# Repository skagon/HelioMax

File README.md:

# HelioMax
HelioMax is a modular extended variation of the classic split mechanical keyboard, ErgoDox. Optimised for detaching the thumb cluster as well as adding an also detachable F-key row. Please note that this is a **wired** keyboard, designed to have the controller and USB connection in a detached central hub.

## Project Architecture

Unlike traditional monolithic keyboard layouts, **HelioMax** breaks the hardware matrix down into standalone, independent modules. This allows the modification of, or iteration upon, individual sections of the keyboard independently, without needing to re-fabricate the entire board. Within the project you will find two main subdirectories, /FFCs and /Pin_Interconnects, containing the HelioMax PCB files and schematics for plain pin interconnects or FFCs (flexible flat cable) via SMD sockets. These are two variations on the subject, and you will see that the routing is **not** visually identical -- however, it is __functionally__ identical.

The second main feature of the HelioMax is the fact that it is designed to be controlled by a single **modified** Raspberry Pi Pico. Each half of the HelioMax consists of the central board, which includes all the communication lines to the controller board, as well as the connections to the thumb cluster and F-key row of its side. The entire half is using a 7×7 integrated matrix and each half is designed to be **independently scanned** by the Pico.

## The Pico

The importance of the "modified" part becomes relevant at this point. The **unmodified** Pico only has **23** consecutive GPIO pins available (GPIO0 - GPIO22). However, two halves of the HelioMax require 2×(7+7)=28 GPIO pins. While this is still attainable using a unified row or column scanning, I really wanted the two halves to be independently scanned. The solution was somewhat easy: the Pico *does* have GPIO23-25 present, only assigned to things redundant for this project. With a soldering iron, a scalpel, and some patience, these pins can be liberated and put to use, the result being a contiguous GPIO space starting at GPIO0 and ending at GPIO28 -- and that leaves **one** extra GPIO to do with as we please.
* **GPIO23**  
  Requires cutting two traces next to TestPoint 4 (TP4) on the underside of the Pico PCB and desoldering one tiny resistor near the microUSB port (R8). The signal is now accessible from TP4!  
* **GPIO24**  
Requires desoldering of two tiny resistors (R1, R10) next to the RP2040 chip and soldering a tiny wire on the bottom (common) pads, which will carry the GPIO24 signal.
* **GPIO25**  
Requires desoldering the LED (D2) and replacing its current-limiting resistor (R3) with a tiny piece of wire (or a solder blob). The GPIO25 signal is now accessible from TP5!

Now, the GPIO range is uninterrupted and at our disposal.

Moreover, the PCB itself needs some slight modification, namely filing down the backplane window, as I have made the choice to include full pads rather than castellated pads, in order to reduce manufacturing cost. The _offending_ pads are meant to connect the TP4 and TP5 of the Pico to the PCB.

The repository includes a legacy 4-in-1 master layout blueprint at the root for spatial configuration, alongside four distinct, decoupled sub-projects representing the four "quadrants":

### The Four Quadrants
* **Praetor Enclave (`/Praetor_Enclave`)**  
  The controller board. Houses the Raspberry Pi Pico micro-controller and connections to the two halves (Rows and Columns) on four separate JST-SH sockets.
* **Corpus Sedes (`/Corpus_Sedes`)**  
  The main mechanical switch matrix body. Serves as the primary foundation for your standard alpha-numeric typing layout.
* **Telorum Belt (`/Telorum_Belt`)**  
  The function top row. Positioned specifically above the main matrix (Corpus Sedes) to the exact position F-keys should be. The connection is regular pins or FFC and can be lined up with mounting holes aligned. Recommending 5mm vertical gap.
* **Pollex Cluster (`/Pollex_Cluster`)**  
  The specialized ergonomic thumb cluster extension, now able to be angled to leverage natural thumb position for primary keys like Space, Enter, Layer control, or whatever suits your typing style. Connects to Corpus Sedes either through pins or FFC.

## Manufacturing & Gerber Instructions

Each directory operates as its own self-contained KiCad project. Choose your poison (FFC or pins) and go to the appropriate subdirectory. No particular instructions needed.

## Licensing & Contributions

This project is open-source. Feel free to clone the repository and spin up custom branches to match your preferred physical desk ergonomics.

## Support the Project
If you find this design useful or want to support future hardware iterations, consider buying me a coffee! Donations most welcome.

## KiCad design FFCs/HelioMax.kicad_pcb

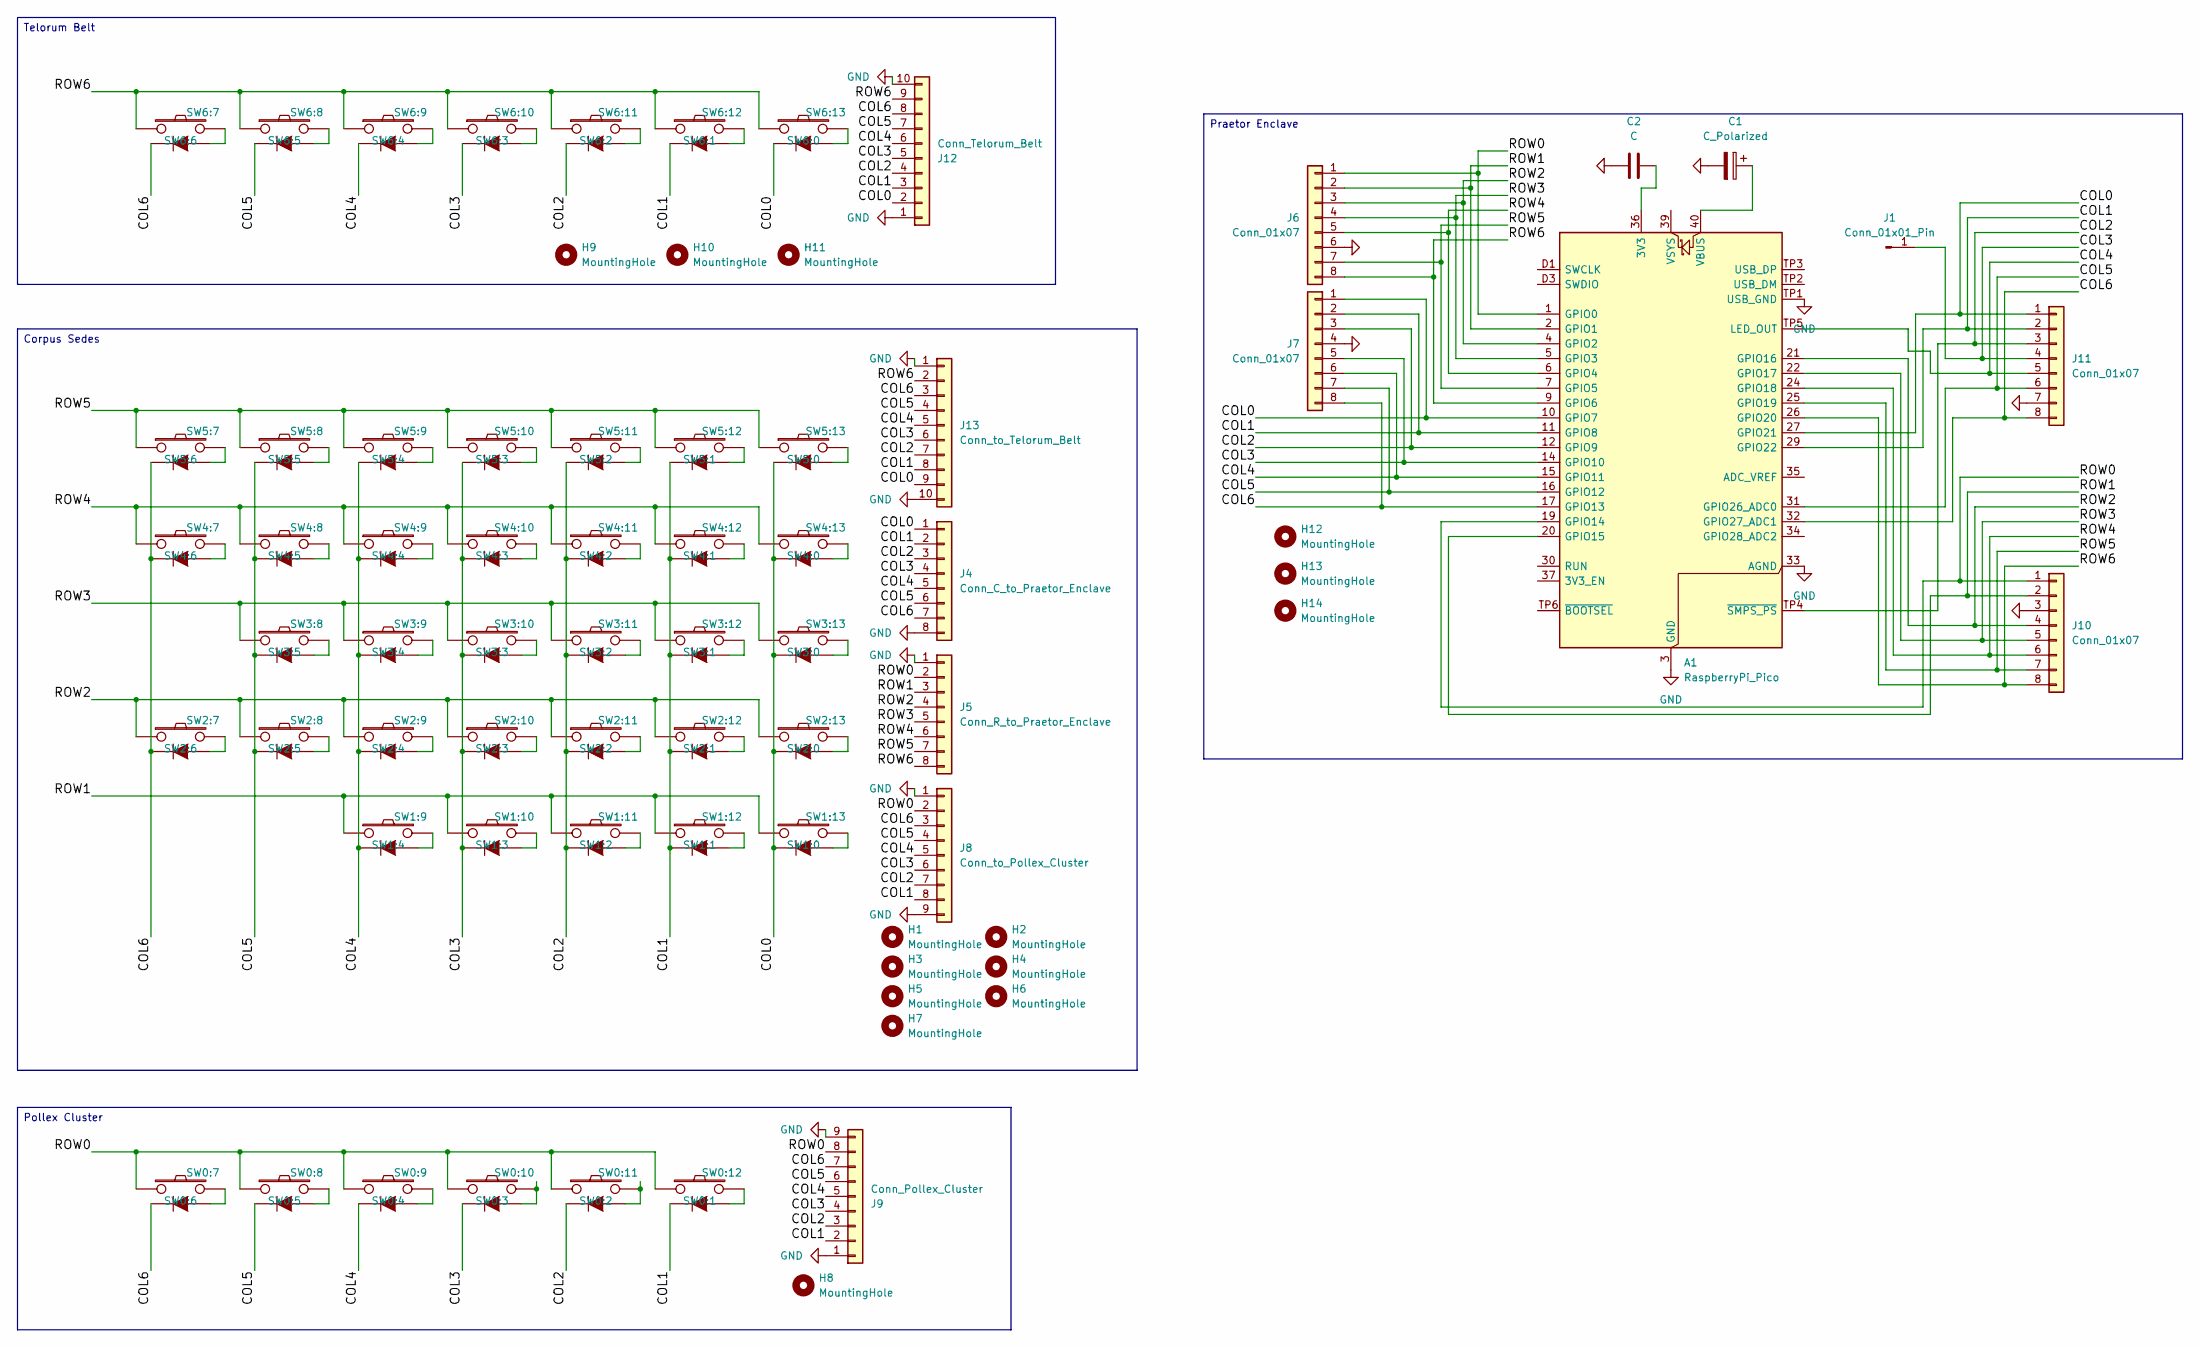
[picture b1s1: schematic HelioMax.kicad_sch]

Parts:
A1: RaspberryPi_Pico; RaspberryPi_Pico_Original_SMD_MountingHoles_HandSolder_Cast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
C1: C_Polarized; CP_Radial_D4.0mm_P2.00mm
C2: C; C_Rect_L7.0mm_W2.5mm_P5.00mm
H1, H2, H3, H4, H5, H6, H7, H8, H9, H10, H11, H12, H13, H14: MountingHole; MountingHole_3.2mm_M3
J1: Conn_01x01_Pin; PinHeader_1x01_P1.00mm_Vertical
J4: Conn_C_to_Praetor_Enclave; JST_SH_SM08B-SRSS-TB_1x08-1MP_P1.00mm_Horizontal
J5: Conn_R_to_Praetor_Enclave; JST_SH_SM08B-SRSS-TB_1x08-1MP_P1.00mm_Horizontal
J6, J7, J10, J11: Conn_01x07; JST_SH_SM08B-SRSS-TB_1x08-1MP_P1.00mm_Horizontal
J8: Conn_to_Pollex_Cluster; Molex_200528-0090_1x09-1MP_P1.00mm_Horizontal
J9: Conn_Pollex_Cluster; Molex_200528-0090_1x09-1MP_P1.00mm_Horizontal
J12: Conn_Telorum_Belt; Molex_200528-0100_1x10-1MP_P1.00mm_Horizontal
J13: Conn_to_Telorum_Belt; Molex_200528-0100_1x10-1MP_P1.00mm_Horizontal
SW0:7: SW0:6; MX_FLIP_CLEAN
SW0:8: SW0:5; MX_FLIP_CLEAN
SW0:9: SW0:4; MX_FLIP_CLEAN
SW0:10: SW0:3; MX_FLIP_CLEAN
SW0:11: SW0:2; MX_FLIP_CLEAN
SW0:12: SW0:1; MX_FLIP_CLEAN
SW1:9: SW1:4; MX_FLIP_CLEAN
SW1:10: SW1:3; MX_FLIP_CLEAN
SW1:11: SW1:2; MX_FLIP_CLEAN
SW1:12: SW1:1; MX_FLIP_CLEAN
SW1:13: SW1:0; MX_FLIP_CLEAN
SW2:7: SW2:6; MX_FLIP_CLEAN
SW2:8: SW2:5; MX_FLIP_CLEAN
SW2:9: SW2:4; MX_FLIP_CLEAN
SW2:10: SW2:3; MX_FLIP_CLEAN
SW2:11: SW2:2; MX_FLIP_CLEAN
SW2:12: SW2:1; MX_FLIP_CLEAN
SW2:13: SW2:0; MX_FLIP_CLEAN
SW3:8: SW3:5; MX_FLIP_CLEAN
SW3:9: SW3:4; MX_FLIP_CLEAN
SW3:10: SW3:3; MX_FLIP_CLEAN
SW3:11: SW3:2; MX_FLIP_CLEAN
SW3:12: SW3:1; MX_FLIP_CLEAN
SW3:13: SW3:0; MX_FLIP_CLEAN
SW4:7: SW4:6; MX_FLIP_CLEAN
SW4:8: SW4:5; MX_FLIP_CLEAN
SW4:9: SW4:4; MX_FLIP_CLEAN
SW4:10: SW4:3; MX_FLIP_CLEAN
SW4:11: SW4:2; MX_FLIP_CLEAN
SW4:12: SW4:1; MX_FLIP_CLEAN
SW4:13: SW4:0; MX_FLIP_CLEAN
SW5:7: SW5:6; MX_FLIP_CLEAN
SW5:8: SW5:5; MX_FLIP_CLEAN
SW5:9: SW5:4; MX_FLIP_CLEAN
SW5:10: SW5:3; MX_FLIP_CLEAN
SW5:11: SW5:2; MX_FLIP_CLEAN
SW5:12: SW5:1; MX_FLIP_CLEAN
SW5:13: SW5:0; MX_FLIP_CLEAN
SW6:7: SW6:6; MX_FLIP_CLEAN
SW6:8: SW6:5; MX_FLIP_CLEAN
SW6:9: SW6:4; MX_FLIP_CLEAN
SW6:10: SW6:3; MX_FLIP_CLEAN
SW6:11: SW6:2; MX_FLIP_CLEAN
SW6:12: SW6:1; MX_FLIP_CLEAN
SW6:13: SW6:0; MX_FLIP_CLEAN

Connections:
/COL0: A1.10 (GPIO7), A1.27 (GPIO21), J4.1, J7.1, J11.1, J12.2, J13.9, SW1:13.4 (K), SW2:13.4 (K), SW3:13.4 (K), SW4:13.4 (K), SW5:13.4 (K), SW6:13.4 (K); also elsewhere on the board
/COL1: A1.11 (GPIO8), A1.29 (GPIO22), J4.2, J7.2, J8.8, J9.2, J11.2, J12.3, J13.8, SW0:12.4 (K), SW1:12.4 (K), SW2:12.4 (K), SW3:12.4 (K), SW4:12.4 (K), SW5:12.4 (K), SW6:12.4 (K); also elsewhere on the board
/COL2: A1.12 (GPIO9), A1.TP4 (~SMPS_PS), J4.3, J7.3, J8.7, J9.3, J11.3, J12.4, J13.7, SW0:11.4 (K), SW1:11.4 (K), SW2:11.4 (K), SW3:11.4 (K), SW4:11.4 (K), SW5:11.4 (K), SW6:11.4 (K); also elsewhere on the board
/COL3: A1.14 (GPIO10), J1.1 (Pin_1_1), J4.4, J7.5, J8.6, J9.4, J11.4, J12.5, J13.6, SW0:10.4 (K), SW1:10.4 (K), SW2:10.4 (K), SW3:10.4 (K), SW4:10.4 (K), SW5:10.4 (K), SW6:10.4 (K); also elsewhere on the board
/COL4: A1.15 (GPIO11), A1.TP5 (LED_OUT), J4.5, J7.6, J8.5, J9.5, J11.5, J12.6, J13.5, SW0:9.4 (K), SW1:9.4 (K), SW2:9.4 (K), SW3:9.4 (K), SW4:9.4 (K), SW5:9.4 (K), SW6:9.4 (K); also elsewhere on the board
/COL5: A1.16 (GPIO12), A1.31 (GPIO26_ADC0), J4.6, J7.7, J8.4, J9.6, J11.6, J12.7, J13.4, SW0:8.4 (K), SW2:8.4 (K), SW3:8.4 (K), SW4:8.4 (K), SW5:8.4 (K), SW6:8.4 (K); also elsewhere on the board
/COL6: A1.17 (GPIO13), A1.32 (GPIO27_ADC1), J4.7, J7.8, J8.3, J9.7, J11.8, J12.8, J13.3, SW0:7.4 (K), SW2:7.4 (K), SW4:7.4 (K), SW5:7.4 (K), SW6:7.4 (K); also elsewhere on the board
/ROW0: A1.1 (GPIO0), A1.19 (GPIO14), J5.2, J6.1, J8.2, J9.8, J10.1, SW0:7.1, SW0:8.1, SW0:9.1, SW0:10.1, SW0:11.1, SW0:12.1; also elsewhere on the board
/ROW1: A1.2 (GPIO1), A1.20 (GPIO15), J5.3, J6.2, J10.2, SW1:9.1, SW1:10.1, SW1:11.1, SW1:12.1, SW1:13.1; also elsewhere on the board
/ROW2: A1.4 (GPIO2), A1.21 (GPIO16), J5.4, J6.3, J10.4, SW2:7.1, SW2:8.1, SW2:9.1, SW2:10.1, SW2:11.1, SW2:12.1, SW2:13.1; also elsewhere on the board
/ROW3: A1.5 (GPIO3), A1.22 (GPIO17), J5.5, J6.4, J10.5, SW3:8.1, SW3:9.1, SW3:10.1, SW3:11.1, SW3:12.1, SW3:13.1; also elsewhere on the board
/ROW4: A1.6 (GPIO4), A1.24 (GPIO18), J5.6, J6.5, J10.6, SW4:7.1, SW4:8.1, SW4:9.1, SW4:10.1, SW4:11.1, SW4:12.1, SW4:13.1; also elsewhere on the board
/ROW5: A1.7 (GPIO5), A1.25 (GPIO19), J5.7, J6.7, J10.7, SW5:7.1, SW5:8.1, SW5:9.1, SW5:10.1, SW5:11.1, SW5:12.1, SW5:13.1; also elsewhere on the board
/ROW6: A1.9 (GPIO6), A1.26 (GPIO20), J5.8, J6.8, J10.8, J12.9, J13.2, SW6:7.1, SW6:8.1, SW6:9.1, SW6:10.1, SW6:11.1, SW6:12.1, SW6:13.1; also elsewhere on the board
GND: A1.3 (GND), A1.8 (GND), A1.13 (GND), A1.18 (GND), A1.23 (GND), A1.28 (GND), A1.33 (AGND), A1.38 (GND), A1.D2 (GND), A1.TP1 (USB_GND), C1.2, C2.2, J4.8, J5.1, J6.6, J6.MP, J7.4, J7.MP, J8.1, J8.9, J8.MP, J9.1, J9.9, J9.MP, J10.3, J10.MP, J11.7, J11.MP, J12.1, J12.10, J12.MP, J13.1, J13.10, J13.MP; also elsewhere on the board
unnamed: A1.36 (3V3), C2.1
unnamed: A1.40 (VBUS), C1.1
unnamed: SW0:7.2, SW0:7.3 (A)
unnamed: SW0:8.2, SW0:8.3 (A)
unnamed: SW0:9.2, SW0:9.3 (A)
unnamed: SW0:10.2, SW0:10.3 (A)
unnamed: SW0:11.2, SW0:11.3 (A)
unnamed: SW0:12.2, SW0:12.3 (A)
unnamed: SW1:9.2, SW1:9.3 (A)
unnamed: SW1:10.2, SW1:10.3 (A)
unnamed: SW1:11.2, SW1:11.3 (A)
unnamed: SW1:12.2, SW1:12.3 (A)
unnamed: SW1:13.2, SW1:13.3 (A)
unnamed: SW2:7.2, SW2:7.3 (A)
unnamed: SW2:8.2, SW2:8.3 (A)
unnamed: SW2:9.2, SW2:9.3 (A)
unnamed: SW2:10.2, SW2:10.3 (A)
unnamed: SW2:11.2, SW2:11.3 (A)
unnamed: SW2:12.2, SW2:12.3 (A)
unnamed: SW2:13.2, SW2:13.3 (A)
unnamed: SW3:8.2, SW3:8.3 (A)
unnamed: SW3:9.2, SW3:9.3 (A)
unnamed: SW3:10.2, SW3:10.3 (A)
unnamed: SW3:11.2, SW3:11.3 (A)
unnamed: SW3:12.2, SW3:12.3 (A)
unnamed: SW3:13.2, SW3:13.3 (A)
unnamed: SW4:7.2, SW4:7.3 (A)
unnamed: SW4:8.2, SW4:8.3 (A)
unnamed: SW4:9.2, SW4:9.3 (A)
unnamed: SW4:10.2, SW4:10.3 (A)
unnamed: SW4:11.2, SW4:11.3 (A)
unnamed: SW4:12.2, SW4:12.3 (A)
unnamed: SW4:13.2, SW4:13.3 (A)
unnamed: SW5:7.2, SW5:7.3 (A)
unnamed: SW5:8.2, SW5:8.3 (A)
unnamed: SW5:9.2, SW5:9.3 (A)
unnamed: SW5:10.2, SW5:10.3 (A)
unnamed: SW5:11.2, SW5:11.3 (A)
unnamed: SW5:12.2, SW5:12.3 (A)
unnamed: SW5:13.2, SW5:13.3 (A)
unnamed: SW6:7.2, SW6:7.3 (A)
unnamed: SW6:8.2, SW6:8.3 (A)
unnamed: SW6:9.2, SW6:9.3 (A)
unnamed: SW6:10.2, SW6:10.3 (A)
unnamed: SW6:11.2, SW6:11.3 (A)
unnamed: SW6:12.2, SW6:12.3 (A)
unnamed: SW6:13.2, SW6:13.3 (A)

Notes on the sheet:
Telorum Belt
Pollex Cluster
Praetor Enclave
Corpus Sedes

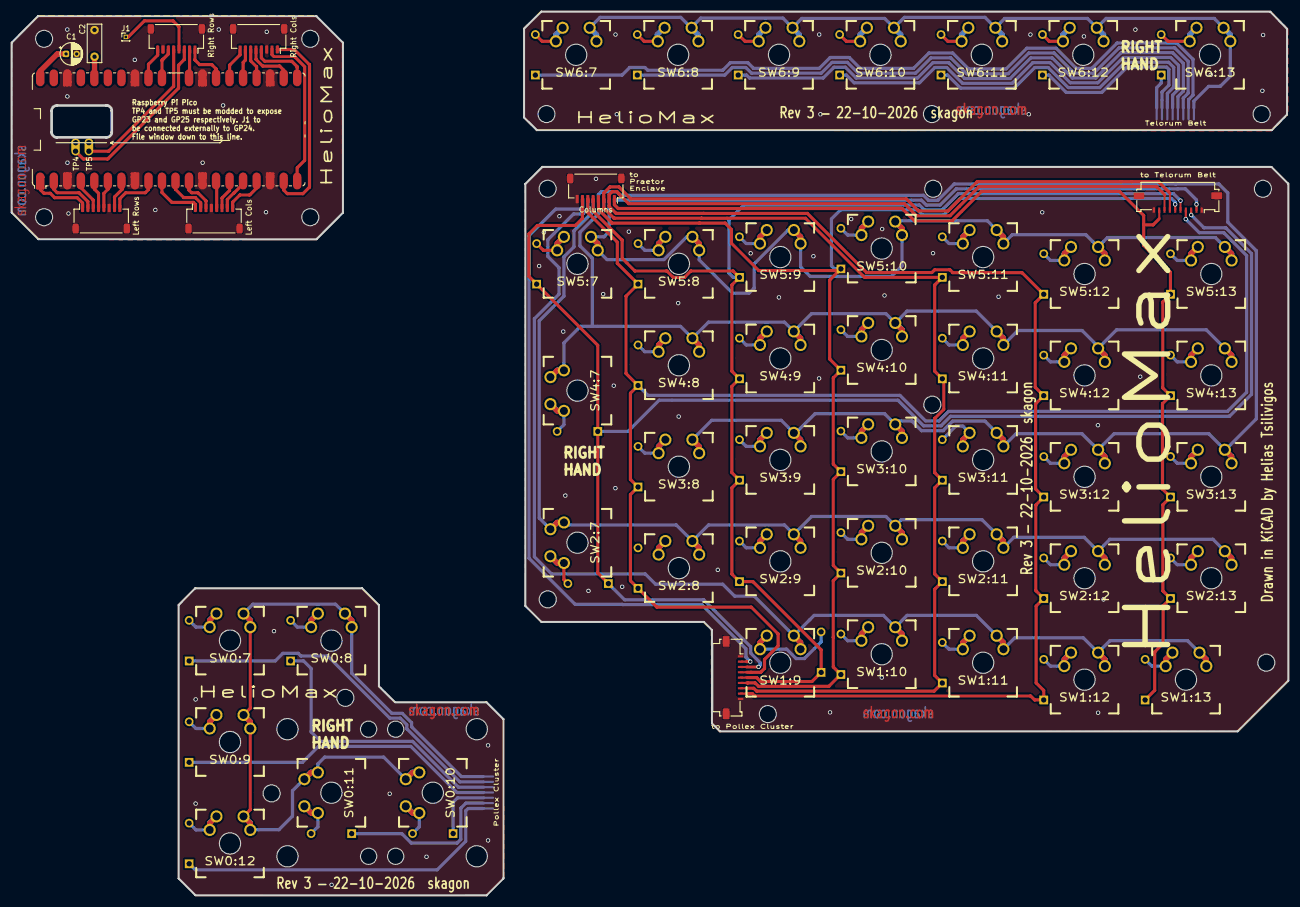
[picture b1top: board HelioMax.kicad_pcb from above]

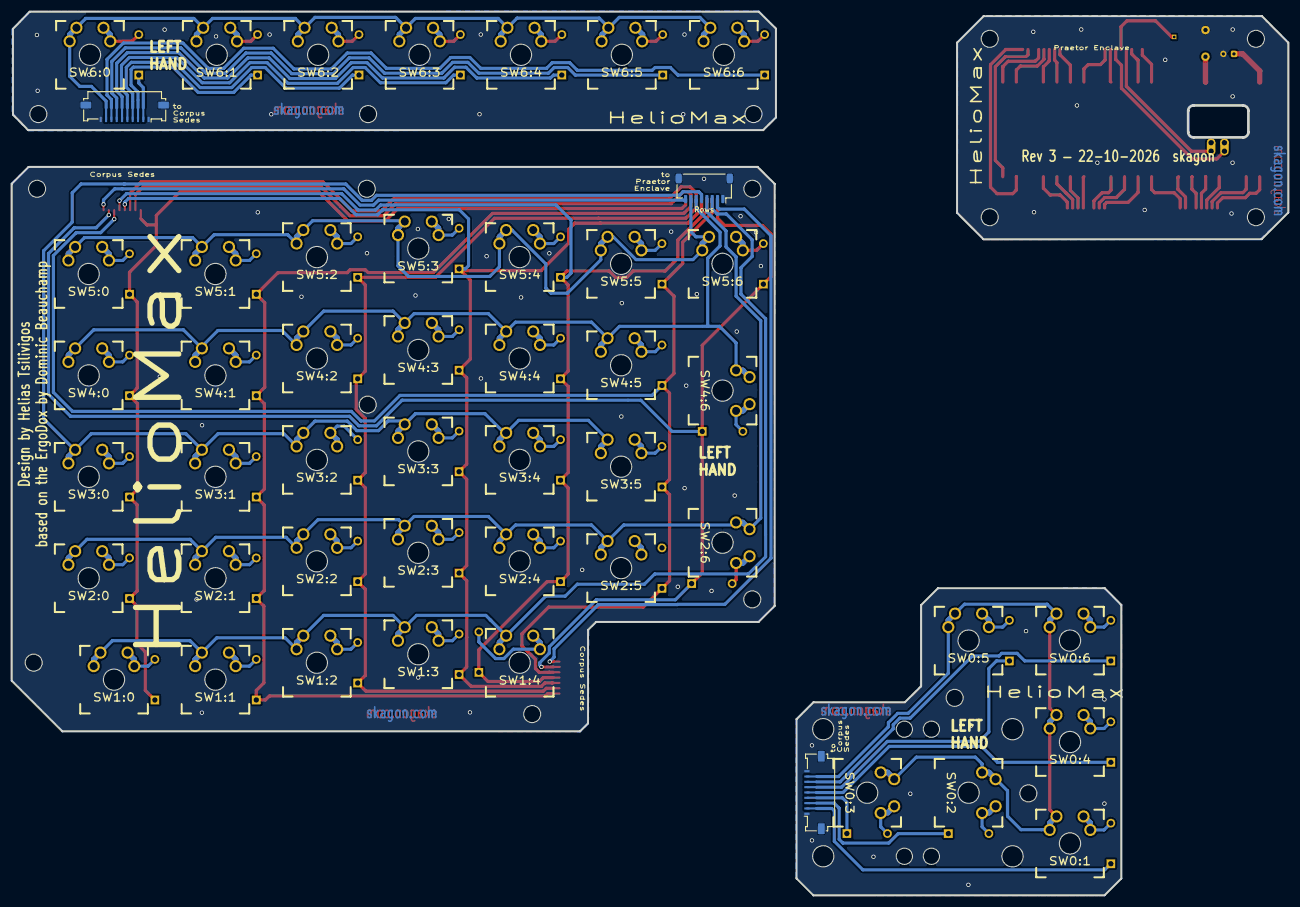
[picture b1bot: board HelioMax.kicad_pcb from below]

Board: 2 copper layers, 239.8 x 166.0 mm, 75 parts (3 on the bottom side), 62 nets.

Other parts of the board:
Columns: Conn_C_to_Praetor_Enclave; JST_SH_SM08B-SRSS-TB_1x08-1MP_P1.00mm_Horizontal
Rows: Conn_R_to_Praetor_Enclave; JST_SH_SM08B-SRSS-TB_1x08-1MP_P1.00mm_Horizontal
S1, S2: STAB200; STAB_PCB940

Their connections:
/COL0: Columns.1; also elsewhere on the board
/COL1: Columns.2; also elsewhere on the board
/COL2: Columns.3; also elsewhere on the board
/COL3: Columns.4; also elsewhere on the board
/COL4: Columns.5; also elsewhere on the board
/COL5: Columns.6; also elsewhere on the board
/COL6: Columns.7; also elsewhere on the board
/ROW0: Rows.2; also elsewhere on the board
/ROW1: Rows.3; also elsewhere on the board
/ROW2: Rows.4; also elsewhere on the board
/ROW3: Rows.5; also elsewhere on the board
/ROW4: Rows.6; also elsewhere on the board
/ROW5: Rows.7; also elsewhere on the board
/ROW6: Rows.8; also elsewhere on the board
GND: Columns.8, Columns.MP, Rows.1, Rows.MP; also elsewhere on the board

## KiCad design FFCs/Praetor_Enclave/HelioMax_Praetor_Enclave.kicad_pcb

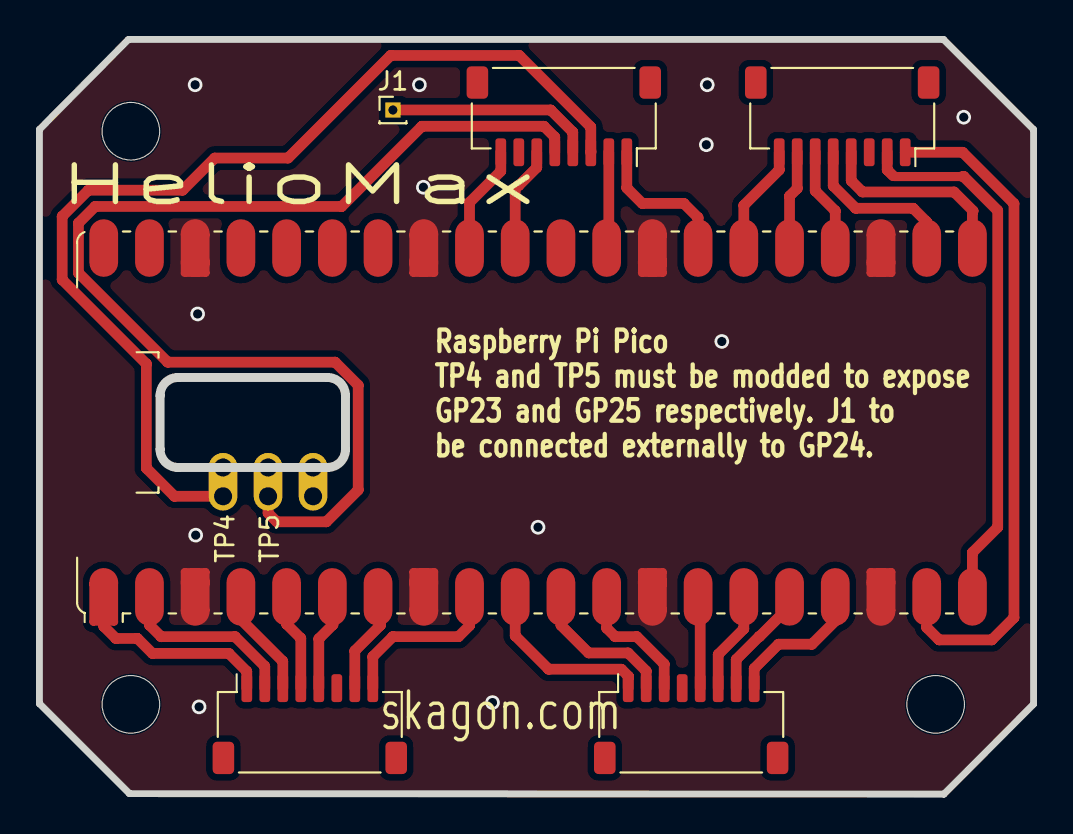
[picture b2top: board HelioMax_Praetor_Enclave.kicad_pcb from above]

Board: 2 copper layers, 55.2 x 41.9 mm, 9 parts (0 on the bottom side), 29 nets.

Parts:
A1: RaspberryPi_Pico; RaspberryPi_Pico_Original_SMD_MountingHoles_HandSolder_Cast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
H12, H13, H14: MountingHole; MountingHole_3.2mm_M3
J1: Conn_01x01_Pin; PinHeader_1x01_P1.00mm_Vertical
J6, J7, J10, J11: Conn_01x07; JST_SH_SM08B-SRSS-TB_1x08-1MP_P1.00mm_Horizontal

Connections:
GND: A1.3 (GND), A1.8 (GND), A1.13 (GND), A1.18 (GND), A1.23 (GND), A1.28 (GND), A1.33 (AGND), A1.38 (GND)
unnamed: A1.1 (GPIO0), J6.1
unnamed: A1.2 (GPIO1), J6.2
unnamed: A1.4 (GPIO2), J6.3
unnamed: A1.5 (GPIO3), J6.4
unnamed: A1.6 (GPIO4), J6.5
unnamed: A1.7 (GPIO5), J6.7
unnamed: A1.9 (GPIO6), J6.8
unnamed: A1.10 (GPIO7), J7.1
unnamed: A1.11 (GPIO8), J7.2
unnamed: A1.12 (GPIO9), J7.3
unnamed: A1.14 (GPIO10), J7.5
unnamed: A1.15 (GPIO11), J7.6
unnamed: A1.16 (GPIO12), J7.7
unnamed: A1.17 (GPIO13), J7.8
unnamed: A1.19 (GPIO14), J10.1
unnamed: A1.20 (GPIO15), J10.2
unnamed: A1.21 (GPIO16), J10.4
unnamed: A1.22 (GPIO17), J10.5
unnamed: A1.24 (GPIO18), J10.6
unnamed: A1.25 (GPIO19), J10.7
unnamed: A1.26 (GPIO20), J10.8
unnamed: A1.27 (GPIO21), J11.1
unnamed: A1.29 (GPIO22), J11.2
unnamed: A1.31 (GPIO26_ADC0), J11.6
unnamed: A1.32 (GPIO27_ADC1), J11.8
unnamed: A1.TP5 (LED_OUT), J11.5
unnamed: A1.TP4 (~SMPS_PS), J11.3
unnamed: J1.1 (Pin_1_1), J11.4
